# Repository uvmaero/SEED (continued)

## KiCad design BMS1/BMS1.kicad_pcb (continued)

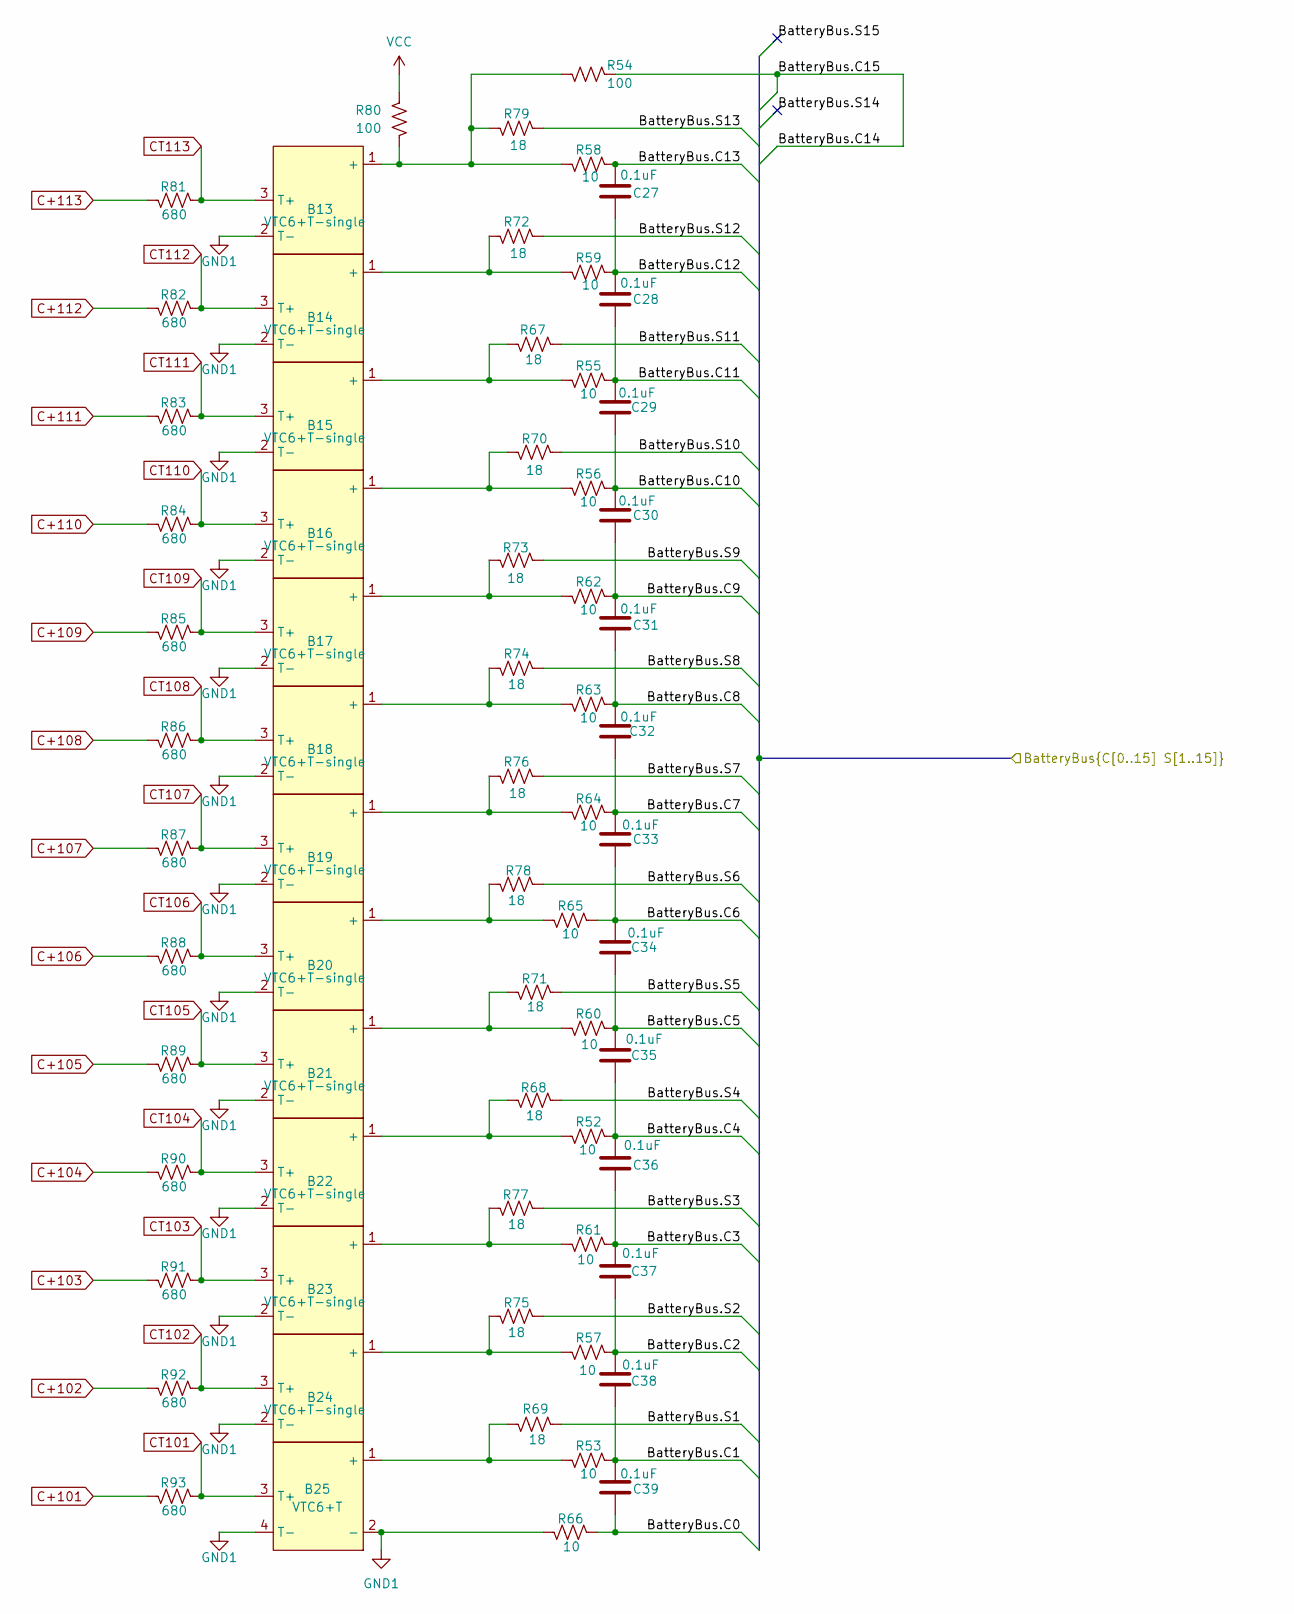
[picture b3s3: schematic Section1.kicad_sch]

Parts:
B13, B14, B15, B16, B17, B18, B19, B20, B21, B22, B23, B24: VTC6+T-single; VTC-6-single
B25: VTC6+T; VTC-6
C27, C28, C29, C30, C31, C32, C33, C34, C35, C36, C37, C38, C39: 0.1uF; C_0603_1608Metric; MPN AGC0603X7R101-104KXP
R52, R53, R55, R56, R57, R58, R59, R60, R61, R62, R63, R64, R65, R66: 10; R_0805_2012Metric; MPN ERJ-P06J100V
R54: 100; R_0805_2012Metric; MPN RMCF0805FT100R
R67, R68, R69, R70, R71, R72, R73, R74, R75, R76, R77, R78: 18; R_2512_6332Metric; MPN RMCF2512FT18R0
R79: 18; R_0603_1608Metric; MPN RMCF2512FT18R0
R80: 100; R_0603_1608Metric; MPN ERJ-3EKF1000V
R81, R82, R83, R84, R85, R86, R87, R88, R89, R90, R91, R92, R93: 680; R_0603_1608Metric; MPN RC0603JR-07680RL

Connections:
/BatteryBus.C0: C39.2, R66.2; also elsewhere on the board
/BatteryBus.C1: C38.2, C39.1, R53.2; also elsewhere on the board
/BatteryBus.C2: C37.2, C38.1, R57.2; also elsewhere on the board
/BatteryBus.C3: C36.2, C37.1, R61.2; also elsewhere on the board
/BatteryBus.C4: C35.2, C36.1, R52.2; also elsewhere on the board
/BatteryBus.C5: C34.2, C35.1, R60.2; also elsewhere on the board
/BatteryBus.C6: C33.2, C34.1, R65.2; also elsewhere on the board
/BatteryBus.C7: C32.1, C33.1, R64.2; also elsewhere on the board
/BatteryBus.C8: C31.2, C32.2, R63.2; also elsewhere on the board
/BatteryBus.C9: C30.2, C31.1, R62.2; also elsewhere on the board
/BatteryBus.C10: C29.2, C30.1, R56.2; also elsewhere on the board
/BatteryBus.C11: C28.2, C29.1, R55.2; also elsewhere on the board
/BatteryBus.C12: C27.2, C28.1, R59.2; also elsewhere on the board
/BatteryBus.C13: C27.1, R58.2; also elsewhere on the board
/BatteryBus.C14: R54.1; also elsewhere on the board
/BatteryBus.S1: R69.2; also elsewhere on the board
/BatteryBus.S2: R75.2; also elsewhere on the board
/BatteryBus.S3: R77.2; also elsewhere on the board
/BatteryBus.S4: R68.2; also elsewhere on the board
/BatteryBus.S5: R71.2; also elsewhere on the board
/BatteryBus.S6: R78.2; also elsewhere on the board
/BatteryBus.S7: R76.2; also elsewhere on the board
/BatteryBus.S8: R74.2; also elsewhere on the board
/BatteryBus.S9: R73.2; also elsewhere on the board
/BatteryBus.S10: R70.2; also elsewhere on the board
/BatteryBus.S11: R67.2; also elsewhere on the board
/BatteryBus.S12: R72.2; also elsewhere on the board
/BatteryBus.S13: R79.2; also elsewhere on the board
C+101: R93.2; also elsewhere on the board
C+102: R92.2; also elsewhere on the board
C+103: R91.2; also elsewhere on the board
C+104: R90.2; also elsewhere on the board
C+105: R89.2; also elsewhere on the board
C+106: R88.2; also elsewhere on the board
C+107: R87.2; also elsewhere on the board
C+108: R86.2; also elsewhere on the board
C+109: R85.2; also elsewhere on the board
C+110: R84.2; also elsewhere on the board
C+111: R83.2; also elsewhere on the board
C+112: R82.2; also elsewhere on the board
C+113: R81.2; also elsewhere on the board
CT101: B25.3 (T+), R93.1; also elsewhere on the board
CT102: B24.3 (T+), R92.1; also elsewhere on the board
CT103: B23.3 (T+), R91.1; also elsewhere on the board
CT104: B22.3 (T+), R90.1; also elsewhere on the board
CT105: B21.3 (T+), R89.1; also elsewhere on the board
CT106: B20.3 (T+), R88.1; also elsewhere on the board
CT107: B19.3 (T+), R87.1; also elsewhere on the board
CT108: B18.3 (T+), R86.1; also elsewhere on the board
CT109: B17.3 (T+), R85.1; also elsewhere on the board
CT110: B16.3 (T+), R84.1; also elsewhere on the board
CT111: B15.3 (T+), R83.1; also elsewhere on the board
CT112: B14.3 (T+), R82.1; also elsewhere on the board
CT113: B13.3 (T+), R81.1; also elsewhere on the board
GND1: B13.2 (T-), B14.2 (T-), B15.2 (T-), B16.2 (T-), B17.2 (T-), B18.2 (T-), B19.2 (T-), B20.2 (T-), B21.2 (T-), B22.2 (T-), B23.2 (T-), B24.2 (T-), B25.2 (-), B25.4 (T-), R66.1; also elsewhere on the board
unnamed: B13.1 (+), R54.2, R58.1, R79.1, R80.2
unnamed: B14.1 (+), R59.1, R72.1
unnamed: B15.1 (+), R55.1, R67.1
unnamed: B16.1 (+), R56.1, R70.1
unnamed: B17.1 (+), R62.1, R73.1
unnamed: B18.1 (+), R63.1, R74.1
unnamed: B19.1 (+), R64.1, R76.1
unnamed: B20.1 (+), R65.1, R78.1
unnamed: B21.1 (+), R60.1, R71.1
unnamed: B22.1 (+), R52.1, R68.1
unnamed: B23.1 (+), R61.1, R77.1
unnamed: B24.1 (+), R57.1, R75.1
unnamed: B25.1 (+), R53.1, R69.1
VCC: R80.1; also elsewhere on the board

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
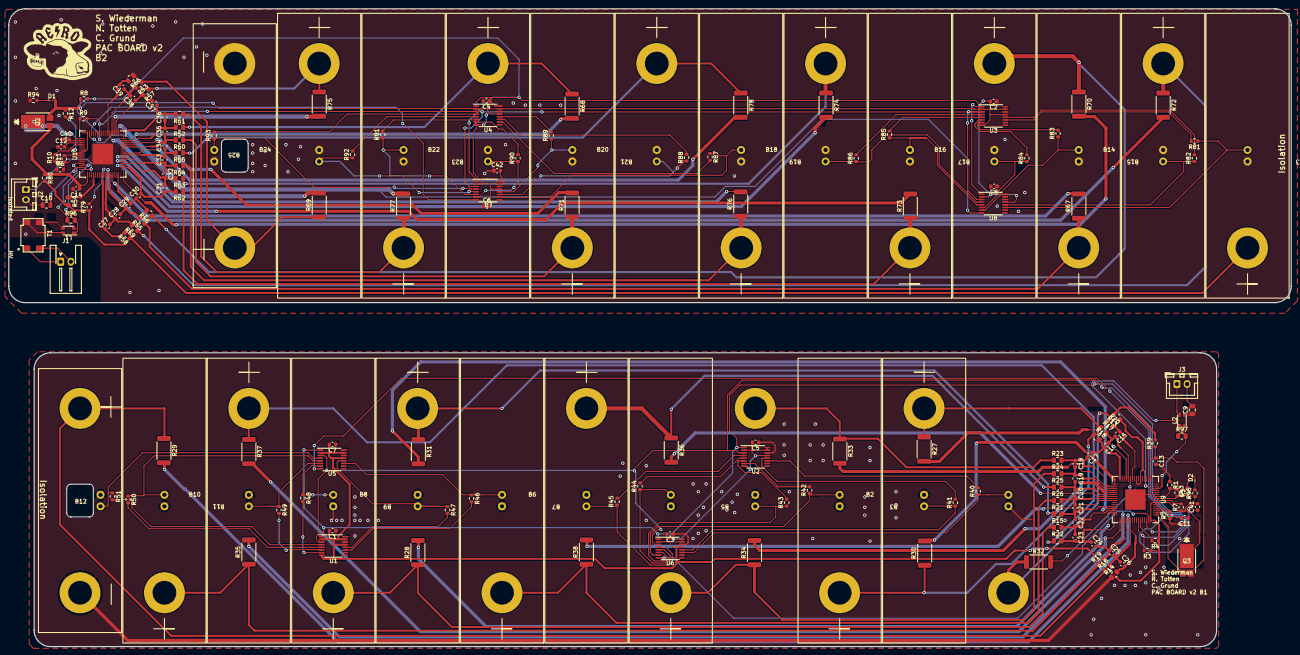
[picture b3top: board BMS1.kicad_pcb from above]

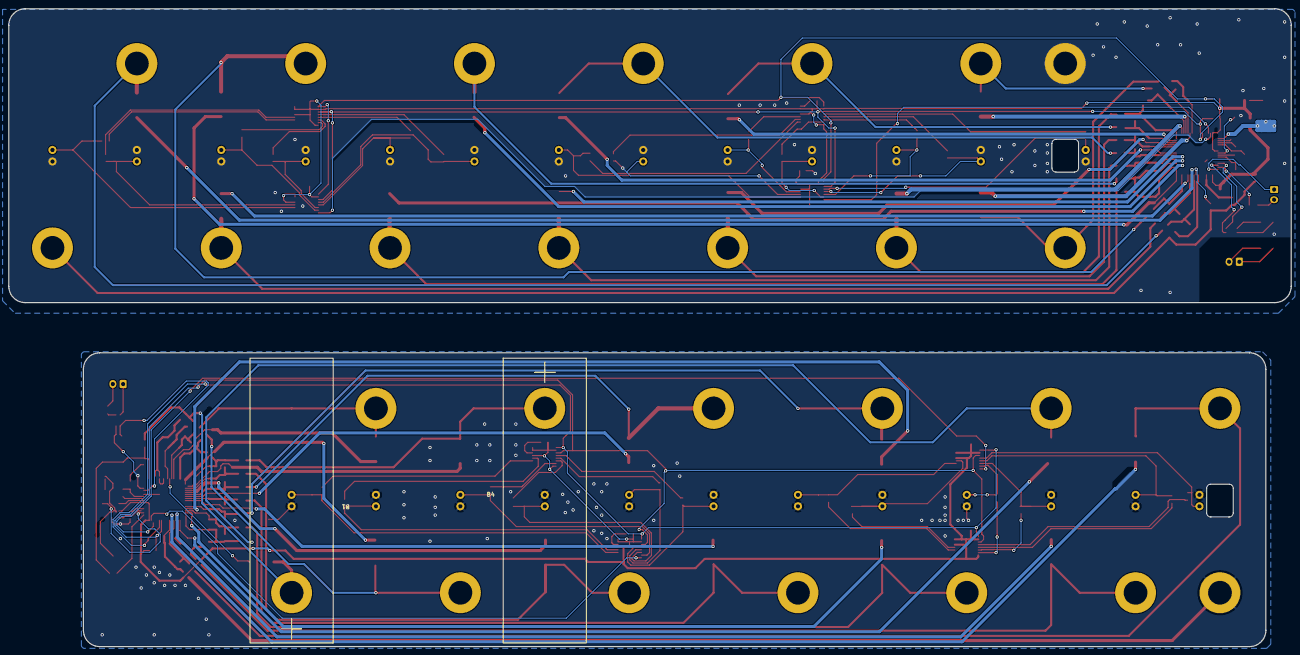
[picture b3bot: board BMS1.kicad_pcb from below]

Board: 2 copper layers, 313.0 x 155.7 mm, 185 parts (2 on the bottom side), 173 nets.

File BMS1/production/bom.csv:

Designator,Footprint,Quantity,Value,LCSC Part #
"B1, B10, B11, B13, B14, B15, B16, B17, B18, B19, B2, B20, B21, B22, B23, B24, B3, B4, B5, B6, B7, B8, B9",VTC-6-single,23,VTC6+T-single,
"B12, B25",VTC-6,2,VTC6+T,
"C1, C13, C14, C15, C16, C17, C18, C19, C2, C20, C21, C22, C23, C24, C25, C26, C27, C28, C29, C3, C30, C31, C32, C33, C34, C35, C36, C37, C38, C39, C4, C5, C6, C7, C8",0603,35,0.1uF,CL10B104KC8NNNC
"C10, C9",0805,2,10nF,C0805C103K5RACTU
"C11, C12, C40, C41, C42, C43",0603,6,1uF,CL10B105KP8NNNC
"D1, D2",0603,2,LED,846-1198-1-ND
J1,JST_XH_S2B-XH-A-1_1x02_P2.50mm_Horizontal,1,Conn_01x02_Horzontal,S2B-XH-A-1
"J2, J3",JST_XH_B2B-XH-A_1x02_P2.50mm_Vertical,2,Conn_01x02_Vertical,B2B-XH-A
"L1, L2",ACT45B-101-2P-TL003_TDK_new,2,Choke_ACT45B-101-2P-TL003,ACT45B-101-2P-TL003
"Q2, Q3",DXT5551P5-13_DIO-M,2,DXT5551P5-13_DIO,DXT5551P5-13
"R1, R10, R11, R2, R5, R6",0603,6,1k,RC0603FR-071KL
"R12, R7",0603,2,1M,ERJ-3EKF1004V
"R13, R54, R96, R97, R98",0805,5,100,RMCF0805FT100R
"R14, R15, R16, R17, R18, R19, R20, R21, R22, R23, R24, R25, R26, R52, R53, R55, R56, R57, R58, R59, R60, R61, R62, R63, R64, R65, R66",0805,27,10,ERJ-P06J100V
"R27, R28, R29, R30, R31, R32, R33, R34, R35, R36, R37, R38, R67, R68, R69, R70, R71, R72, R73, R74, R75, R76, R77, R78, R79",2512,25,18,RMCF2512FT18R0
"R3, R4, R8, R9",0603,4,20k,ERJ-3EKF2002V
"R39, R80",0603,2,100,RC0603FR-07100RL
"R40, R41, R42, R43, R44, R45, R46, R47, R48, R49, R50, R51, R81, R82, R83, R84, R85, R86, R87, R88, R89, R90, R91, R92, R93",0603,25,680,RC0603JR-07680RL
"R94, R95",0603,2,330,ERA-3AEB331V
T1,SOIC4_CBM4D19_SUM,1,ESMIT-4180_C,ESMIT-4180/C
"U1, U2, U3, U4, U5, U6, U7, U8",TSSOP-16_4.4x5mm_P0.65mm,8,ADG728,ADG728BRUZ-REEL7
"U10, U9",QFP-64_11x11_Pitch0.5mm,2,LTC6812-1,LTC6812ILWE-1#3ZZTRPBF

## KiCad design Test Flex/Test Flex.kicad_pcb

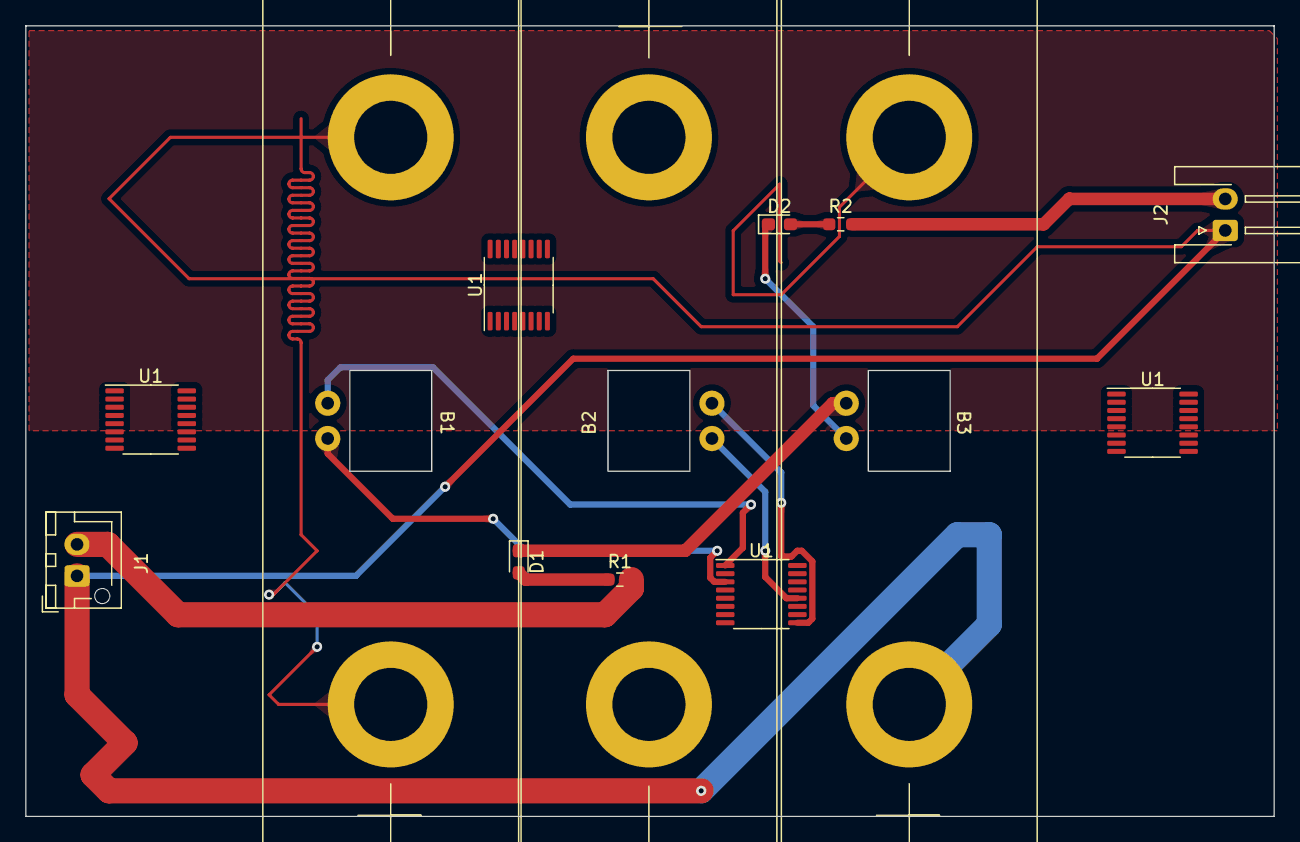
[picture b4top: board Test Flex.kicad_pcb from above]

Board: 2 copper layers, 99.1 x 62.7 mm, 13 parts (0 on the bottom side), 11 nets.

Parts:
B1, B2, B3: VTC6+T; VTC-6
D1, D2: LED; LED_0603_1608Metric_Pad1.05x0.95mm_HandSolder
J1: Conn_01x02; JST_XH_B2B-XH-AM_1x02_P2.50mm_Vertical
J2: Conn_01x02; JST_XH_S2B-XH-A-1_1x02_P2.50mm_Horizontal
R1, R2: R_US; R_0603_1608Metric_Pad0.98x0.95mm_HandSolder
U1, U1#2, U1#3, U1#4: ADG728; TSSOP-16_4.4x5mm_P0.65mm

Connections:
GND: B1.1 (+), B1.2 (-), B3.1 (+), J1.1, J2.1
unnamed: B1.3 (T+), U1#2.1 (SCL)
unnamed: B1.4 (T-), U1#2.3 (SDA)
unnamed: B2.3 (T+), U1#2.12 (S5)
unnamed: B2.4 (T-), U1#2.9 (S8)
unnamed: B3.3 (T+), D1.1 (K)
unnamed: B3.4 (T-), D2.1 (K)
unnamed: D1.2 (A), R1.1
unnamed: D2.2 (A), R2.1
unnamed: J1.2, R1.2
unnamed: J2.2, R2.2

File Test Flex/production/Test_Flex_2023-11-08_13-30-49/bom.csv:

Designator,Footprint,Quantity,Value,LCSC Part #
"B1, B2, B3",VTC-6,3,VTC6+T,
"D1, D2",0603,2,LED,
J1,JST_XH_B2B-XH-AM_1x02_P2.50mm_Vertical,1,Conn_01x02,
J2,JST_XH_S2B-XH-A-1_1x02_P2.50mm_Horizontal,1,Conn_01x02,
"R1, R2",0603,2,R_US,
"U1_4, U1_3, U1_2, U1",TSSOP-16_4.4x5mm_P0.65mm,4,ADG728,

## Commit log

2023-10-03 BMS update
2023-10-04 two strings
2023-10-09 sprint 1 push
2023-10-09 Created MainBMS
2023-10-10 BMS rev1
2023-10-12 start footprint
2023-10-13 footy?
2023-10-24 footprint
2023-10-25 SChematic to sheets
2023-10-25 First Iteration of Main Board
2023-10-26 Vias it is
2023-10-27 Post Design Review
2023-11-07 Cap Change
2023-11-08 smol made
2023-11-09 Everybody is in their general local!
2023-11-10 First PCB Revision
2023-11-10 Added Code and README file
2023-11-10 Adding code
2023-11-19 V1 Layout!
2023-12-31 Schematic (Self) Review Done
2024-02-26 fixed footy
2024-04-18 final before comp
2024-04-19 fixed to whats on board footy not changed
2024-11-14 Added text
2024-11-15 Meeting 11/14/24
2025-01-30 Deleted cell shorts
2025-01-30 GPIO pin correction
2025-01-30 added chokes
2025-01-31 Changed board creator names
2025-01-31 Changed board name on PCB
2025-02-02 Ran ERC
2025-02-04 BigDaddy Meeting
2025-02-06 ERC fixes
2025-02-06 ERC error fixes
2025-02-07 Footprints
2025-02-07 updated choke symbol and footprint
2025-02-07 Update fp-info-cache
2025-02-07 rotated chokes and added datasheet info, changed a couple footprints
2025-02-07 resaved
2025-02-07 updated datasheets and MPNs
2025-02-09 changed R18ohm footprints
2025-02-13 PCB Routing
2025-02-19 Routing
2025-02-23 MOre Routinggggg
2025-02-24 more fucking routing
2025-02-26 DRC fixes
2025-02-28 DRC error fixes
2025-02-28 BOM updates
2025-03-01 HV LV isol dimensions
2025-03-02 Finishing Touches!
    Updated trace widths. Board is ready order. IDK what im gonna do with all this free time now, maybe get my life back?
2025-04-04 updated precharge board
    - added C5, C6 and changed C1 and C2 to 0.1u
    - added 2k pullup resistors to MOSI pins
    - pulled Slow to GND, deleted the switch
    - updated the capacitor and resistor footprints
    -----------we need to remake the PCB. Will need physical dimensions from last board. Also will need to consult p23 of the LTC6820 datasheet for for spacing and ground plane considerations
2025-04-04 precharge 2025 update
    updated precharge board
    - added C5, C6 and changed C1 and C2 to 0.1u
    - added 2k pullup resistors to MOSI pins
    - pulled Slow to GND, deleted the switch
    - updated the capacitor and resistor footprints
    -----------we need to remake the PCB. Will need physical dimensions from last board. Also will need to consult p23 of the LTC6820 datasheet for for spacing and ground plane considerations
2025-04-04 deleted bad folder
2025-04-04 updating precharge
2025-04-04 Pre-charge routing
2025-05-03 Added System Block Diagram
